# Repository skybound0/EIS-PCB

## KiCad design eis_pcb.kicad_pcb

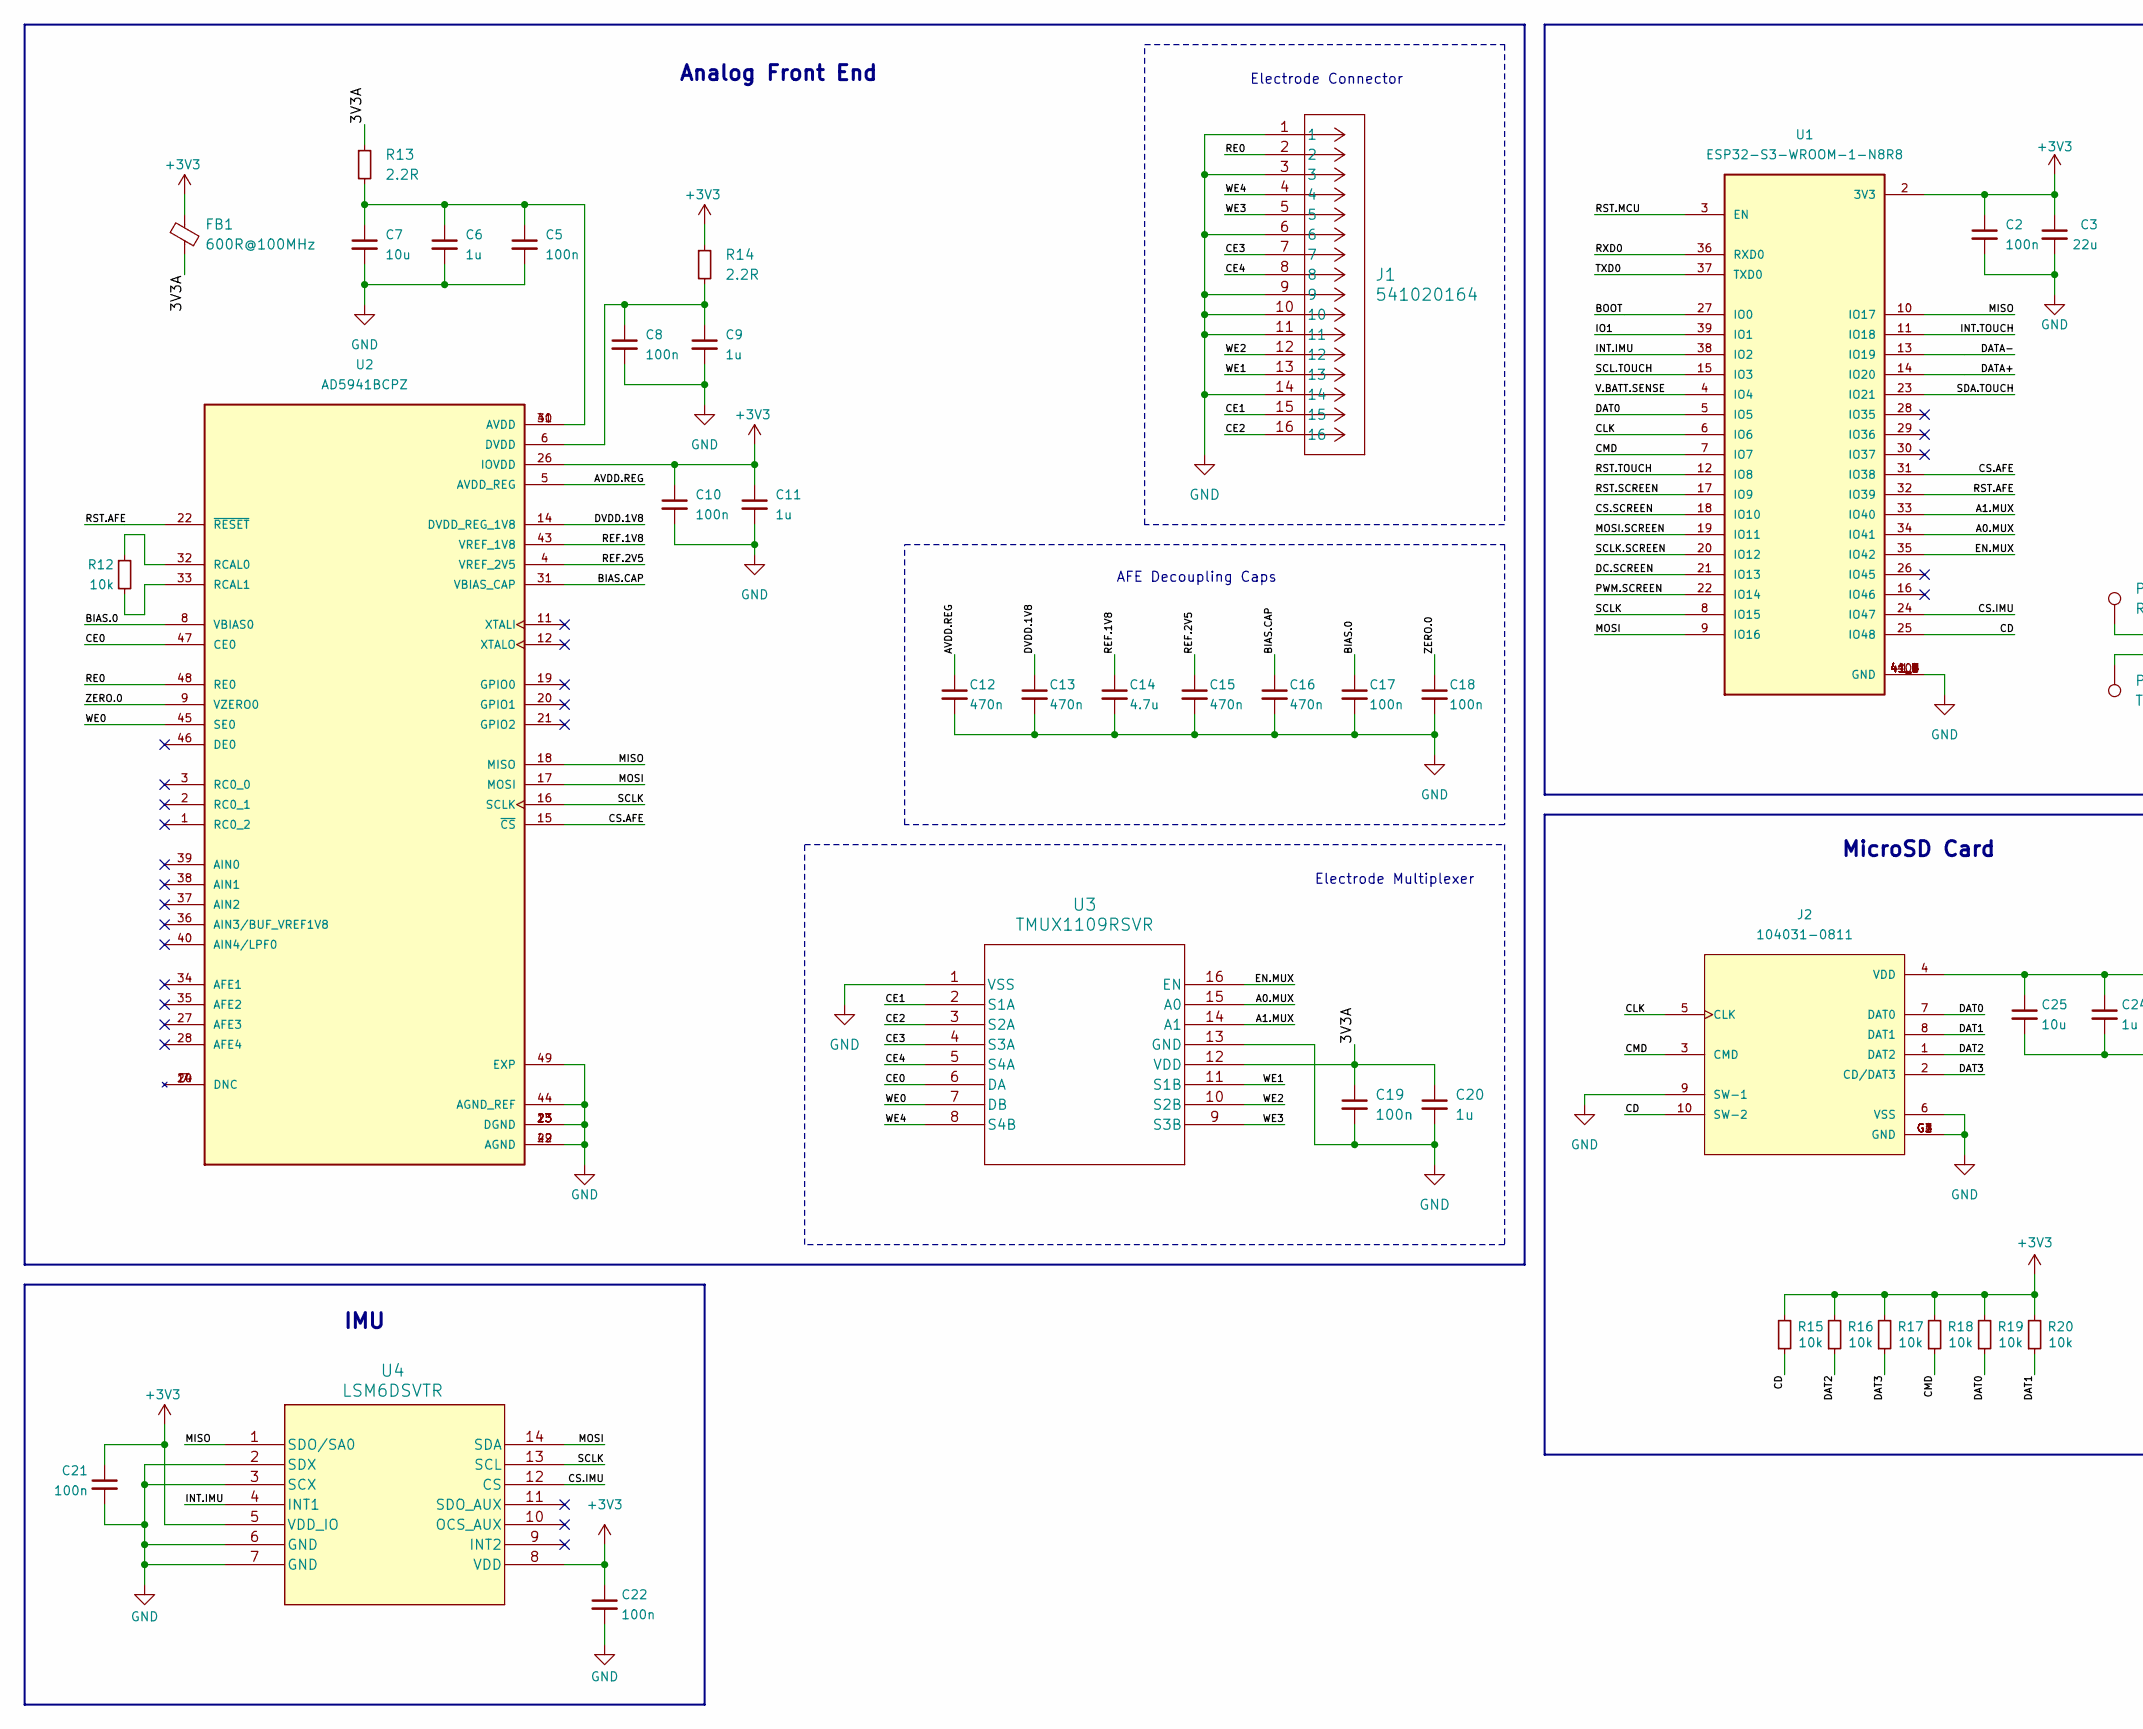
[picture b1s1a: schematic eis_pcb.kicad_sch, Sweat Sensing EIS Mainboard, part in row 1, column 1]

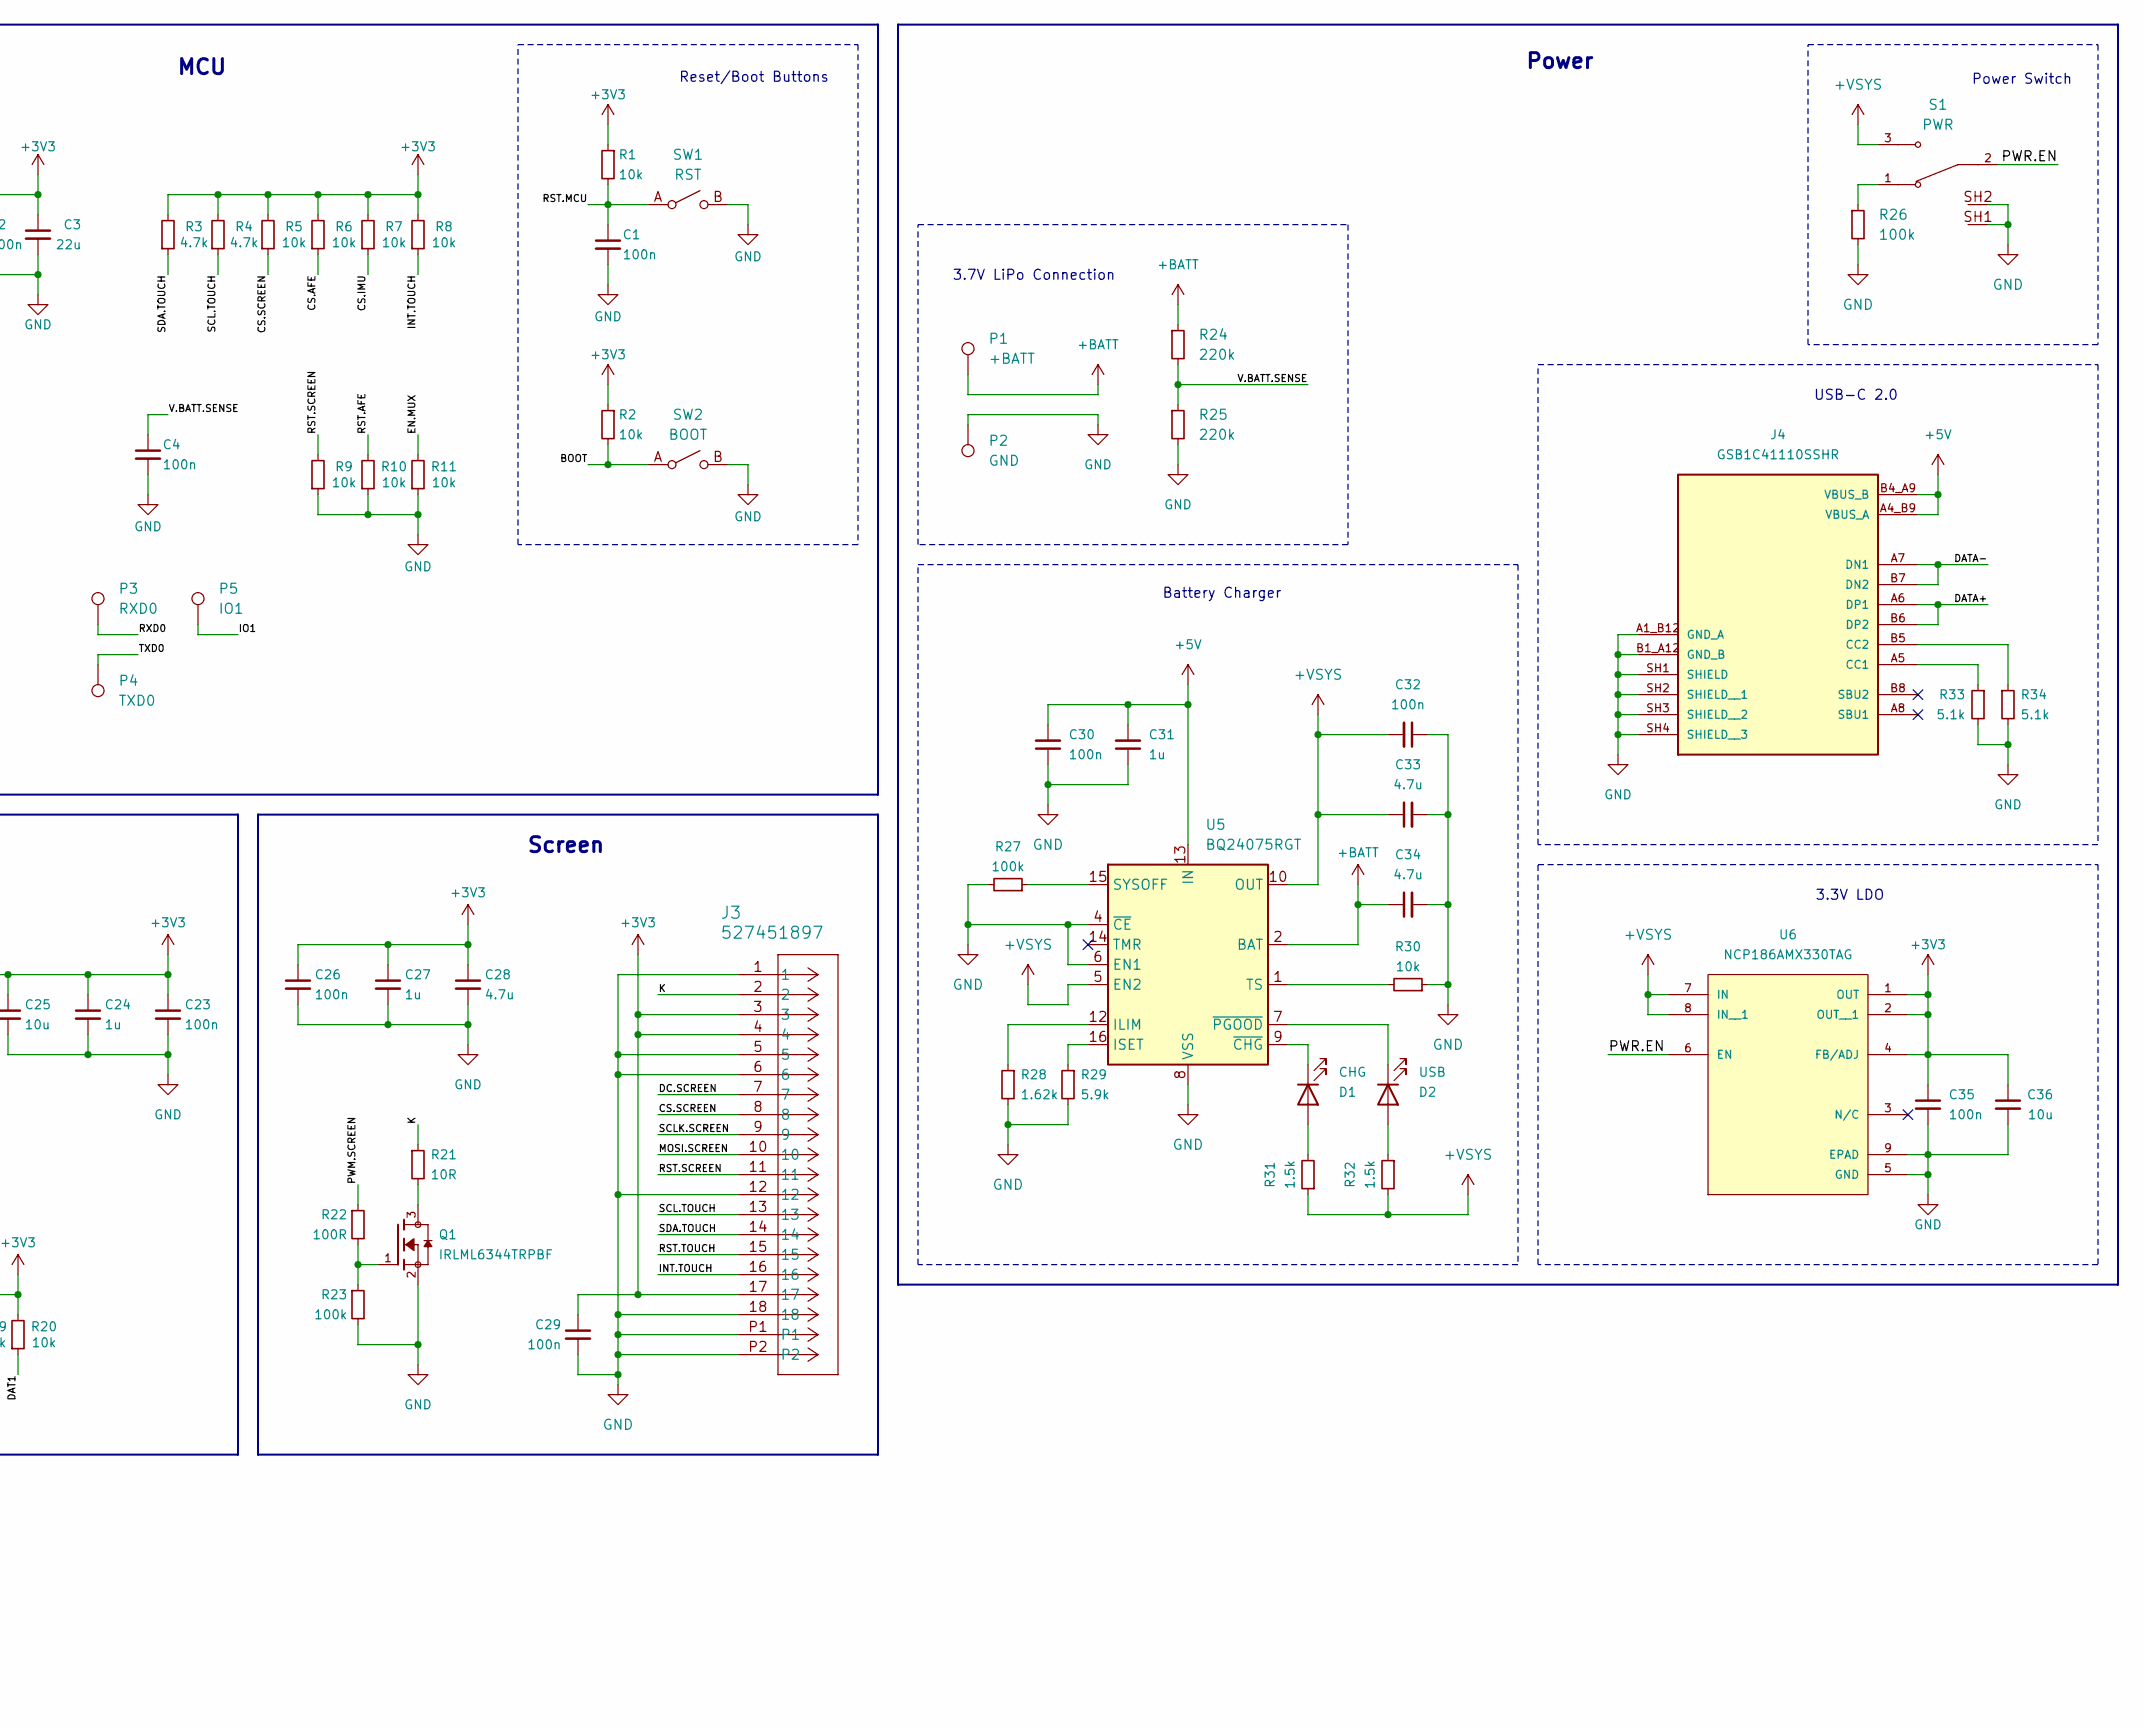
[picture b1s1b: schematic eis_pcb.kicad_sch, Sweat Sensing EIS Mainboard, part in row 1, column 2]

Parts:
C1, C2, C4, C5, C8, C10, C17, C18, C19, C21, C22, C23, C26, C29, C30, C32, C35: 100n; C_0402_1005Metric
C3: 22u; C_0603_1608Metric
C6, C9, C11, C20, C24, C27, C31: 1u; C_0603_1608Metric
C7, C25, C36: 10u; C_0603_1608Metric
C12, C13, C15, C16: 470n; C_0402_1005Metric
C14, C28, C33, C34: 4.7u; C_0603_1608Metric
D1: CHG; LED_0603_1608Metric
D2: USB; LED_0603_1608Metric
FB1: 600R@100MHz; D_0805_2012Metric
J1: 541020164; CON_541020164
J2: 104031-0811; MOLEX_104031-0811; PARTREV B2; DigiKey_Part_Number WM6357CT-ND
J3: 527451897; CON_527451897_MOL
J4: GSB1C41110SSHR; AMPHENOL_GSB1C41110SSHR; PARTREV AX1
P1: +BATT; TestPoint_THTPad_D2.0mm_Drill1.0mm
P2: GND; TestPoint_THTPad_D2.0mm_Drill1.0mm
P3: RXD0; TestPoint_Pad_D1.5mm
P4: TXD0; TestPoint_Pad_D1.5mm
P5: IO1; TestPoint_Pad_D1.5mm
Q1: IRLML6344TRPBF; TRANS_IRLML6344TRPBF; PARTREV December 19, 2014; DigiKey_Part_Number IRLML6344TRPBFCT-ND
R1, R2, R5, R6, R7, R8, R9, R10, R11, R15, R16, R17, R18, R19, R20, R30: 10k; R_0402_1005Metric
R3, R4: 4.7k; R_0402_1005Metric
R12: 10k; R_0805_2012Metric
R13, R14: 2.2R; R_0402_1005Metric
R21: 10R; R_0402_1005Metric
R22: 100R; R_0402_1005Metric
R23, R26, R27: 100k; R_0402_1005Metric
R24, R25: 220k; R_0402_1005Metric
R28: 1.62k; R_0402_1005Metric
R29: 5.9k; R_0402_1005Metric
R31, R32: 1.5k; R_0402_1005Metric
R33, R34: 5.1k; R_0402_1005Metric
S1: PWR; SW_SLW-864587-2A-RA-N-D; PARTREV 1.01
SW1: RST; R-667995_MIT
SW2: BOOT; R-667995_MIT
U1: ESP32-S3-WROOM-1-N8R8; ESP32-S3-WROOM-1; DigiKey_Part_Number 5407-ESP32-S3-WROOM-1-N8R8CT-ND
U2: AD5941BCPZ; QFN50P700X700X80-49N; PARTREV B
U3: TMUX1109RSVR; RSV16_TEX
U4: LSM6DSVTR; LGA14-L_2P59X3P1X0P5_STM
U5: BQ24075RGT; VQFN-16-1EP_3x3mm_P0.5mm_EP1.6x1.6mm
U6: NCP186AMX330TAG; PSON40P160X120X45-9N; PARTREV Rev.5

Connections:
+3V3: C2.1, C3.1, C10.1, C11.1, C21.1, C22.1, C23.1, C24.1, C25.1, C26.1, C27.1, C28.1, C29.1, C35.1, C36.1, FB1.1, J2.4 (VDD), J3.3, J3.4, J3.17, R1.1, R2.1, R3.2, R4.2, R5.2, R6.2, R7.2, R8.2, R14.1, R15.2, R16.2, R17.2, R18.2, R19.2, R20.2, U1.2 (3V3), U2.26 (IOVDD), U4.5 (VDD_IO), U4.8 (VDD), U6.1 (OUT), U6.2 (OUT__1), U6.4 (FB/ADJ)
+5V: C30.2, C31.2, J4.A4_B9 (VBUS_A), J4.B4_A9 (VBUS_B), U5.13 (IN)
+BATT: C34.1, P1.1 (1_1), R24.1, U5.2 (BAT), U5.3 (BAT)
+VSYS: C32.2, C33.1, R31.1, R32.2, S1.3, U5.5 (EN2), U5.10 (OUT), U5.11 (OUT), U6.7 (IN), U6.8 (IN__1)
/3V3A: C19.1, C20.1, FB1.2, R13.1, U3.12 (VDD)
/A0.MUX: U1.34 (IO41), U3.15 (A0)
/A1.MUX: U1.33 (IO40), U3.14 (A1)
/AVDD.REG: C12.1, U2.5 (AVDD_REG)
/BIAS.0: C17.1, U2.8 (VBIAS0)
/BIAS.CAP: C16.1, U2.31 (VBIAS_CAP)
/BOOT: R2.2, SW2.A, U1.27 (IO0)
/CD: J2.10 (SW-2), R15.1, U1.25 (IO48)
/CE0: U2.47 (CE0), U3.6 (DA)
/CE1: J1.15, U3.2 (S1A)
/CE2: J1.16, U3.3 (S2A)
/CE3: J1.7, U3.4 (S3A)
/CE4: J1.8, U3.5 (S4A)
/CLK: J2.5 (CLK), U1.6 (IO6)
/CMD: J2.3 (CMD), R18.1, U1.7 (IO7)
/CS.AFE: R6.1, U1.31 (IO38), U2.15 (~CS)
/CS.IMU: R7.1, U1.24 (IO47), U4.12 (CS)
/CS.SCREEN: J3.8, R5.1, U1.18 (IO10)
/DAT0: J2.7 (DAT0), R19.1, U1.5 (IO5)
/DAT1: J2.8 (DAT1), R20.1
/DAT2: J2.1 (DAT2), R16.1
/DAT3: J2.2 (CD/DAT3), R17.1
/DATA+: J4.A6 (DP1), J4.B6 (DP2), U1.14 (IO20)
/DATA-: J4.A7 (DN1), J4.B7 (DN2), U1.13 (IO19)
/DC.SCREEN: J3.7, U1.21 (IO13)
/DVDD.1V8: C13.1, U2.14 (DVDD_REG_1V8)
/EN.MUX: R11.2, U1.35 (IO42), U3.16 (EN)
/INT.IMU: U1.38 (IO2), U4.4 (INT1)
/INT.TOUCH: J3.16, R8.1, U1.11 (IO18)
/IO1: P5.1 (1_1), U1.39 (IO1)
/K: J3.2, R21.1
/MISO: U1.10 (IO17), U2.18 (MISO), U4.1 (SDO/SA0)
/MOSI: U1.9 (IO16), U2.17 (MOSI), U4.14 (SDA)
/MOSI.SCREEN: J3.10, U1.19 (IO11)
/PWM.SCREEN: R22.1, U1.22 (IO14)
/PWR.EN: S1.2, U6.6 (EN)
/RE0: J1.2, U2.48 (RE0)
/REF.1V8: C14.1, U2.43 (VREF_1V8)
/REF.2V5: C15.1, U2.4 (VREF_2V5)
/RST.AFE: R10.2, U1.32 (IO39), U2.22 (~RESET)
/RST.MCU: C1.1, R1.2, SW1.A, U1.3 (EN)
/RST.SCREEN: J3.11, R9.2, U1.17 (IO9)
/RST.TOUCH: J3.15, U1.12 (IO8)
/RXD0: P3.1 (1_1), U1.36 (RXD0)
/SCL.TOUCH: J3.13, R4.1, U1.15 (IO3)
/SCLK: U1.8 (IO15), U2.16 (SCLK), U4.13 (SCL)
/SCLK.SCREEN: J3.9, U1.20 (IO12)
/SDA.TOUCH: J3.14, R3.1, U1.23 (IO21)
/TXD0: P4.1 (1_1), U1.37 (TXD0)
/V.BATT.SENSE: C4.1, R24.2, R25.1, U1.4 (IO4)
/WE0: U2.45 (SE0), U3.7 (DB)
/WE1: J1.13, U3.11 (S1B)
/WE2: J1.12, U3.10 (S2B)
/WE3: J1.5, U3.9 (S3B)
/WE4: J1.4, U3.8 (S4B)
/ZERO.0: C18.1, U2.9 (VZERO0)
GND: C1.2, C2.2, C3.2, C4.2, C5.2, C6.2, C7.2, C8.2, C9.2, C10.2, C11.2, C12.2, C13.2, C14.2, C15.2, C16.2, C17.2, C18.2, C19.2, C20.2, C21.2, C22.2, C23.2, C24.2, C25.2, C26.2, C27.2, C28.2, C29.2, C30.1, C31.1, C32.1, C33.2, C34.2, C35.2, C36.2, J1.1, J1.3, J1.6, J1.9, J1.10, J1.11, J1.14, J2.6 (VSS), J2.9 (SW-1), J2.G1 (GND), J2.G2 (GND), J2.G3 (GND), J2.G4 (GND), J3.1, J3.5, J3.6, J3.12, J3.18, J3.P1, J3.P2, J4.A1_B12 (GND_A), J4.B1_A12 (GND_B), J4.SH1 (SHIELD), J4.SH2 (SHIELD__1), J4.SH3 (SHIELD__2), J4.SH4 (SHIELD__3), P2.1 (1_1), Q1.2, R9.1, R10.1, R11.1, R23.2, R25.2, R26.2, R27.2, R28.2, R29.2, R30.1, R33.2, R34.2, S1.SH1, S1.SH2, SW1.B, SW2.B, U1.1 (GND), U1.40 (GND), U1.41_1 (GND), U1.41_2 (GND), U1.41_3 (GND), U1.41_4 (GND), U1.41_5 (GND), U1.41_6 (GND), U1.41_7 (GND), U1.41_8 (GND), U1.41_9 (GND), U2.13 (DGND), U2.23 (DGND), U2.25 (DGND), U2.29 (AGND), U2.42 (AGND), U2.44 (AGND_REF), U2.49 (EXP), U3.1 (VSS), U3.13 (GND), U4.2 (SDX), U4.3 (SCX), U4.6 (GND), U4.7 (GND), U5.4 (~CE), U5.6 (EN1), U5.8 (VSS), U5.17 (VSS), U6.5 (GND), U6.9 (EPAD)
unnamed: C5.1, C6.1, C7.1, R13.2, U2.30 (AVDD), U2.41 (AVDD)
unnamed: D1.2 (A), R31.2
unnamed: D1.1 (K), U5.9 (~CHG)
unnamed: D2.2 (A), R32.1
unnamed: D2.1 (K), U5.7 (~PGOOD)
unnamed: J4.A5 (CC1), R33.1
unnamed: J4.B5 (CC2), R34.1
unnamed: Q1.1, R22.2, R23.1
unnamed: Q1.3, R21.2
unnamed: R26.1, S1.1
unnamed: C8.1, C9.1, R14.2, U2.6 (DVDD)
unnamed: R12.1, U2.32 (RCAL0)
unnamed: R12.2, U2.33 (RCAL1)
unnamed: R28.1, U5.12 (ILIM)
unnamed: R29.1, U5.16 (ISET)
unnamed: R27.1, U5.15 (SYSOFF)
unnamed: R30.2, U5.1 (TS)

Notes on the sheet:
MCU
Screen
AFE Decoupling Caps
3.3V LDO
USB-C 2.0
Electrode Multiplexer
IMU
Analog Front End
Power
Electrode Connector
Reset/Boot Buttons
Power Switch
MicroSD Card
3.7V LiPo Connection
Battery Charger

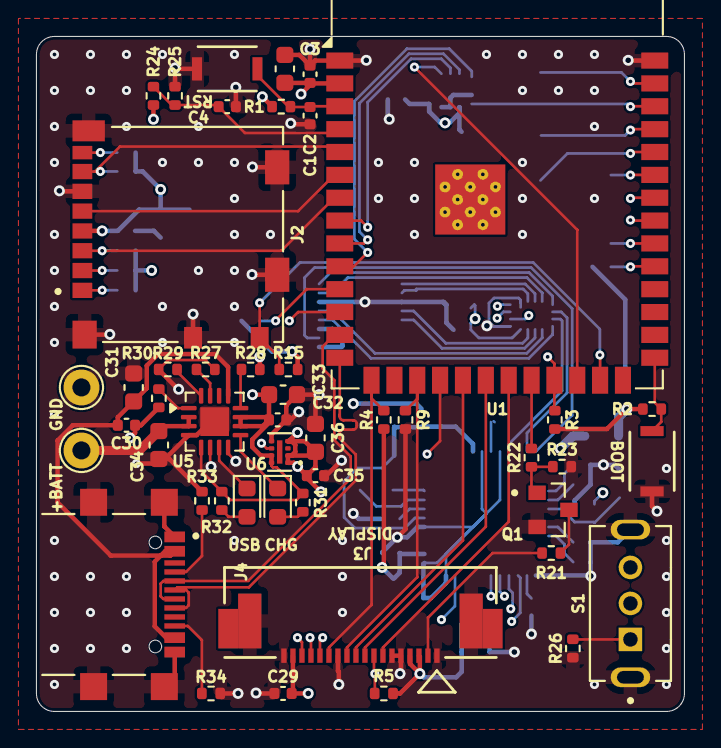
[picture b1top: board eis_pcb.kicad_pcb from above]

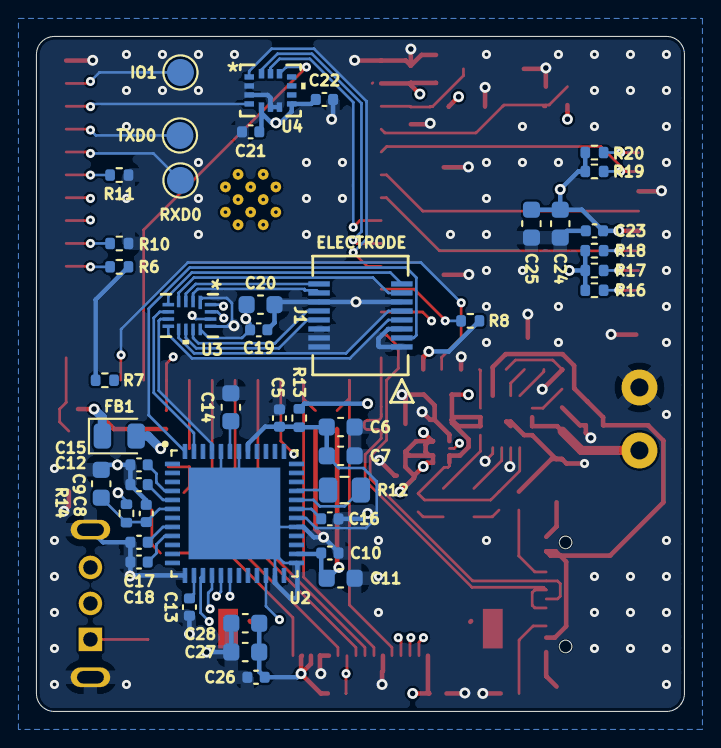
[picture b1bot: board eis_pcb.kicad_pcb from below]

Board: 6 copper layers, 36.0 x 37.5 mm, 92 parts (45 on the bottom side), 78 nets.

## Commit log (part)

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2025-11-24 Finished PCB with manufacturing files in production folder
2025-11-24 Removed battery zone
2026-01-02 Final PCB
2026-02-23 final board
2026-06-18 update for multiplexed electrodes
    - fix boot/reset buttons
    - fix IMU
    - add multiplexer
    - add mezzanine electrode PCB connector
    - add power path management circuit
2026-06-18 update power circuit
    - switch to BQ24075 charge controller with integrated DPPM
    - add 2.8V LDO for display
2026-06-19 remove 2.8v circuitry
    turns out it wasnt need it. my chud life
2026-06-23 complete noise suppression, begin layout
2026-06-24 finish rev B schematic
    did some layout planning
2026-06-24 remove redundant caps
    removed some decoupling caps in power circuit because the components were so close together
2026-06-24 begin power layout
2026-06-25 finish layout
2026-06-30 fix drc/net errors, add via stitching
